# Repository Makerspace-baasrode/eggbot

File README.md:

# eggbot
a drawing machine using eggs as a canvas

This is a project that started in with a build about 10 years ago.
So in this repository you will find a section of old reference files, of which I can not guarantee that they are still functional. But I rather include them to let you wander around to discover what is our there.
I know that a lot of the software will no longere be functional and needs an update, but I'd liked to keep them here as a reference to what was used 10+ years ago

The new build we are attempting in 2025 will be in the top level. 
It will be structured in the several technices we are going to use, CAD-model, 3D-print, laser cutting, PCB design, PCB assembling, ...

If there is any suggestion to organize it differently please let me know

## original project

this project is a make over of the [Eval Mad Scientists](https://shop.evilmadscientist.com/productsmenu/766) eggbot project. All credits go to them as the originators of the ideas. (https://hackaday.com/2019/04/17/what-can-you-learn-from-an-eggbot/)

## refenced links
### The original
- [The Original Egg-Bot Kit](https://wiki.evilmadscientist.com/The_Original_Egg-Bot_Kit)

### 3D prints
- [Enhanced penholder for SphereBot](https://www.thingiverse.com/thing:13407)
- [Laser Cut Sphere-o-bot](https://www.thingiverse.com/thing:368403#files)
- [Laser Cut Sphere-o-bot Instructables](https://www.instructables.com/Laser-Cut-Sphere-O-Bot/)
- [Fischer Technik Eggbot](https://www.thingiverse.com/thing:8109)
- [Eggcup holders for SphereBot / Completely Printable Eggbot](https://www.thingiverse.com/thing:13960)
- [Completely printable Egg-drawer](https://www.thingiverse.com/thing:7988)
- [Finucane Derivative Eggbot](https://www.thingiverse.com/thing:65753)

### Drawing
- [StippleGen](https://wiki.evilmadscientist.com/StippleGen)
- [StippleGen: Weighted Voronoi](https://www.evilmadscientist.com/2012/stipplegen-weighted-voronoi-stippling-and-tsp-paths-in-processing/)
- [code and designs](https://github.com/davidbliss/eggbot)

### Software
- [SphereBotSenderProcessing](https://github.com/zaggo/SphereBotSenderProcessing)
- [Eggduino](https://github.com/cocktailyogi/EggDuino/)
- [Eggbotsimulator](https://github.com/gabber1/EggbotSimulator)
- [EBB Commands](https://www.schmalzhaus.com/EBB/EBBCommands.html)

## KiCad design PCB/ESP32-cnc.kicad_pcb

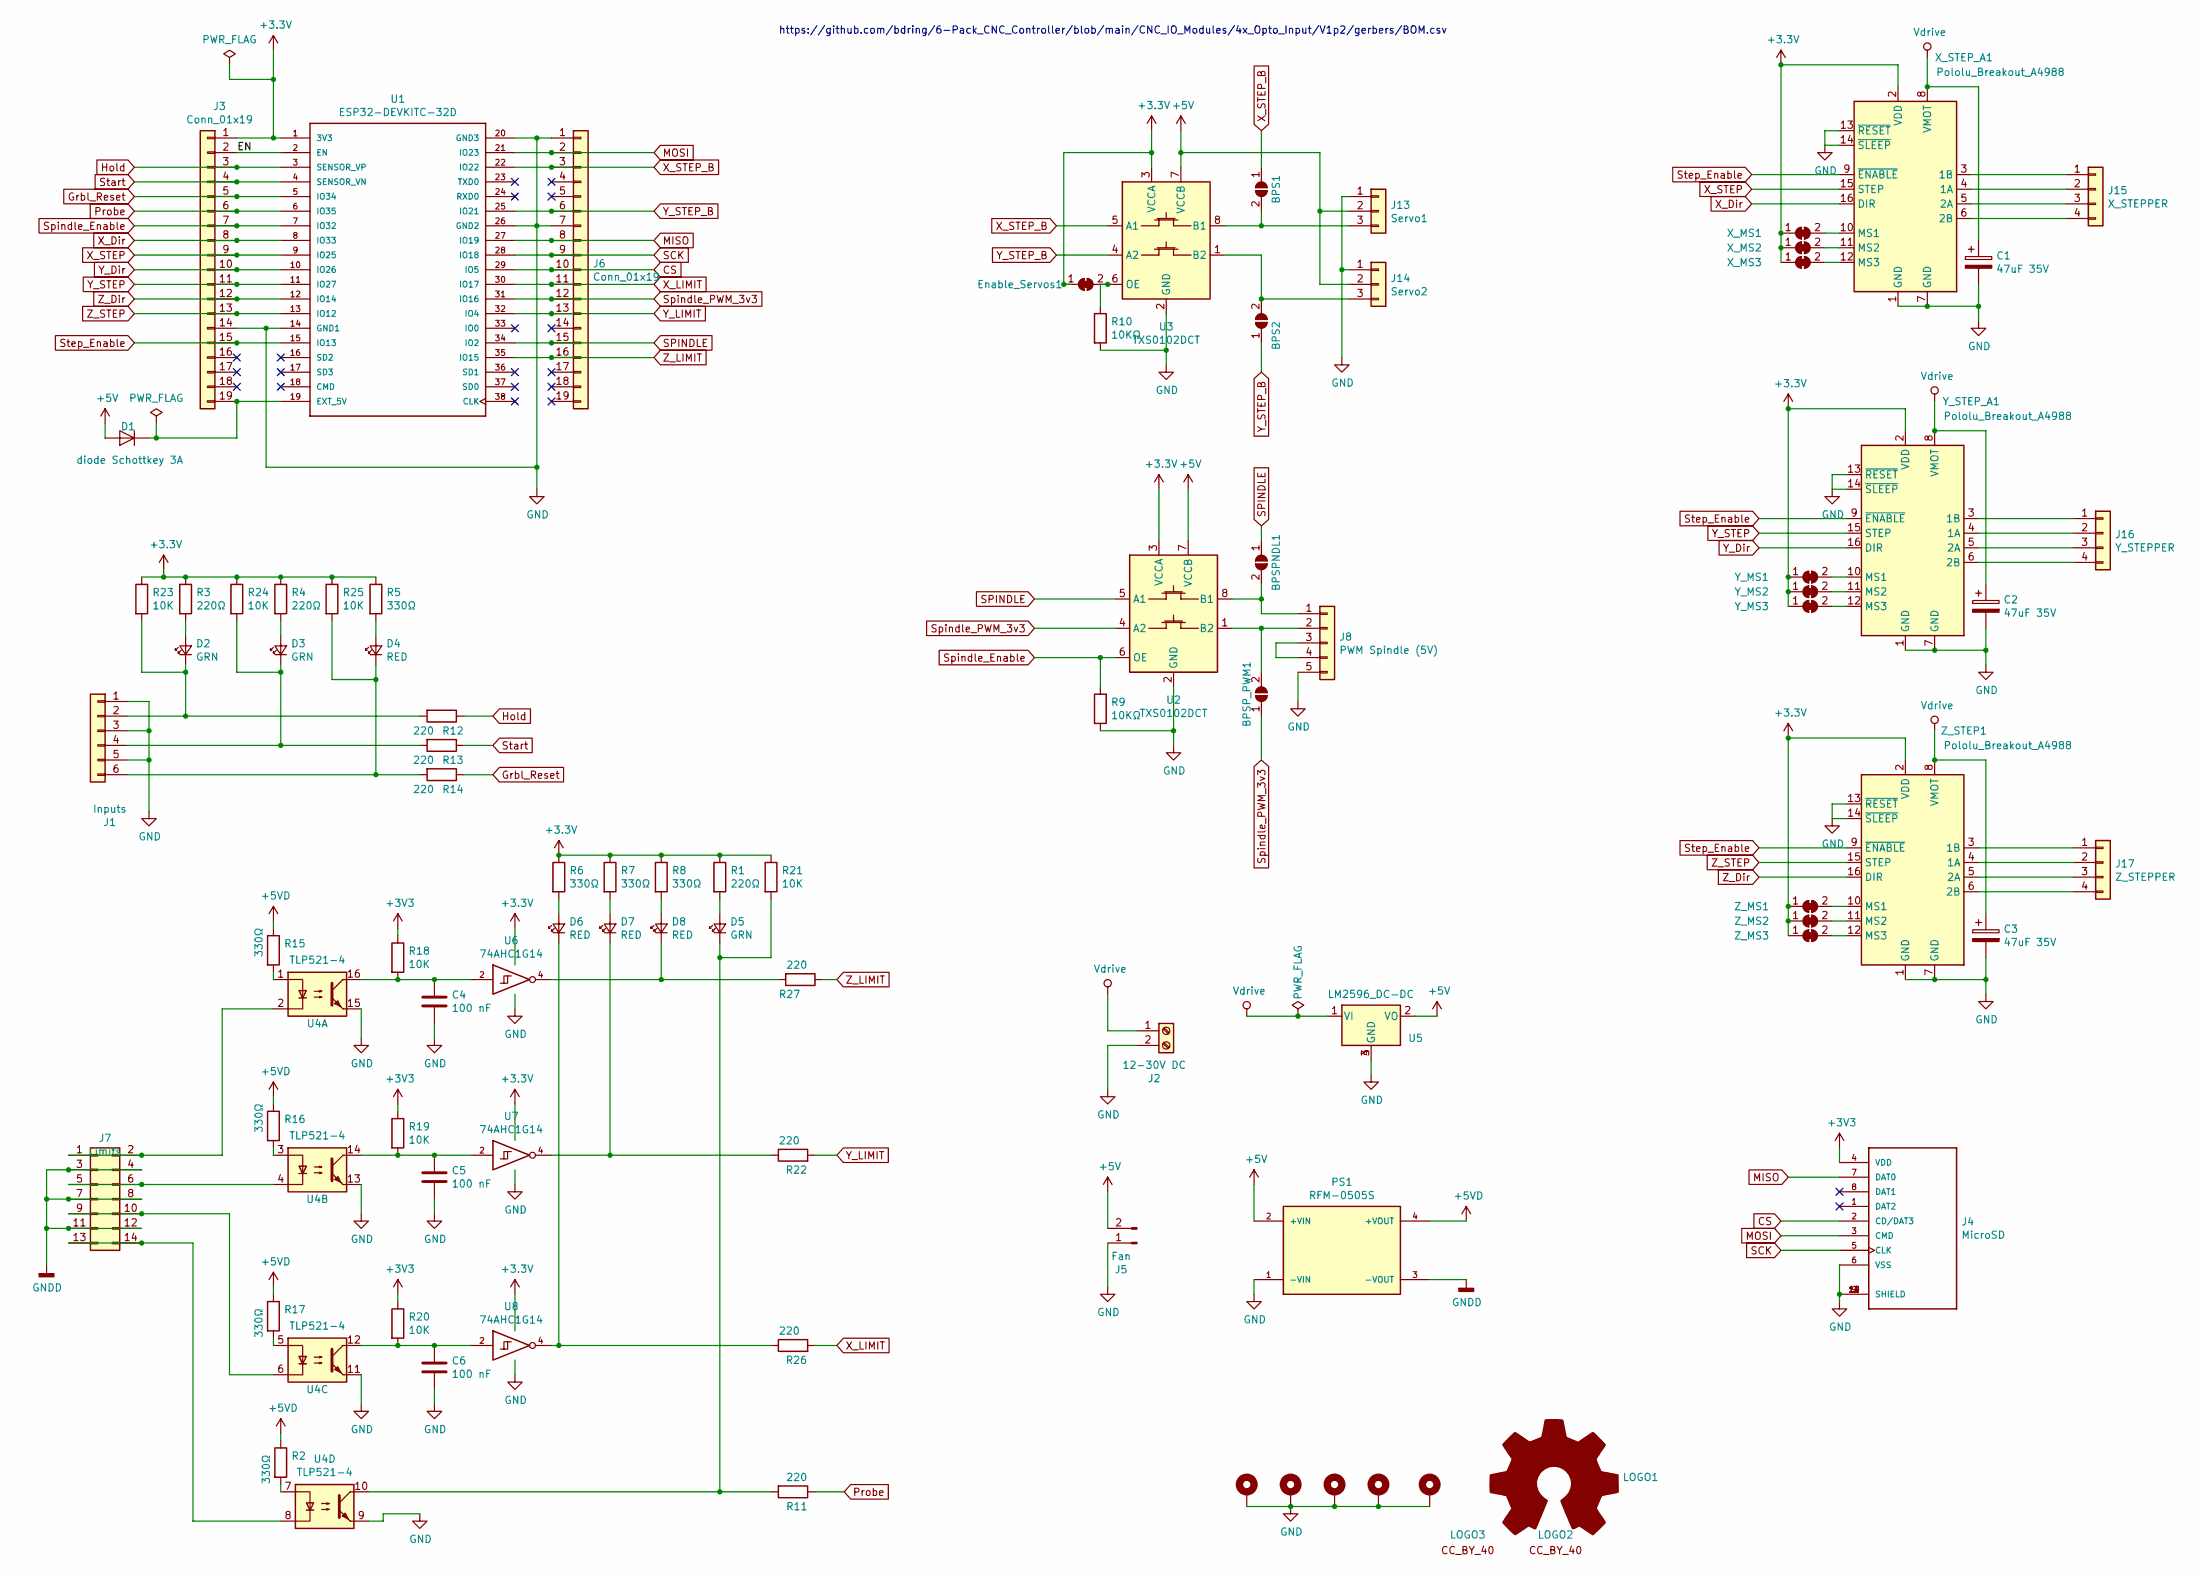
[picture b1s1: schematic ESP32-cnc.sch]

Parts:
BPS1: SERVO1; SolderJumper-2_P1.3mm_Open_TrianglePad1.0x1.5mm
BPS2: SERVO2; SolderJumper-2_P1.3mm_Open_TrianglePad1.0x1.5mm
BPSPNDL1: SPNDL_ON; SolderJumper-2_P1.3mm_Open_TrianglePad1.0x1.5mm
BPSP_PWM1: SPNDL_PWM; SolderJumper-2_P1.3mm_Open_TrianglePad1.0x1.5mm
C1, C2, C3: 47uF 35V; CP_Radial_D10.0mm_P5.00mm; LCSC C134832
C4, C5, C6: 100 nF; C_0805_2012Metric_Pad1.15x1.40mm_HandSolder
D1: diode Schottkey 3A; D_SMA; LCSC C64982
D2, D3, D5: GRN; LED_1206_HandSoldering
D4, D6, D7, D8: RED; LED_1206_HandSoldering
Enable_Servos1: Enable_Servos; SolderJumper-2_P1.3mm_Bridged_RoundedPad1.0x1.5mm
H1, H2, H3, H4, H5: MountingHole_Pad; MountingHole_8.4mm_M8_Pad_Via
J1: Inputs; PinHeader_1x06_P2.54mm_Vertical
J2: 12-30V DC; TerminalBlock_Altech_AK300-2_P5.00mm
J3, J6: Conn_01x19; PinHeader_1x19_P2.54mm_Vertical
J4: MicroSD; GCT_MEM2067-02-180-00-A_REVB; LCSC C91145
J5: Fan; PinHeader_1x02_P2.54mm_Vertical
J7: Limits; PinHeader_2x07_P2.54mm_Vertical
J8: PWM Spindle (5V); PinHeader_1x05_P2.54mm_Vertical
J13: Servo1; PinHeader_1x03_P2.54mm_Vertical
J14: Servo2; PinHeader_1x03_P2.54mm_Vertical
J15: X_STEPPER; PinHeader_1x04_P2.54mm_Vertical
J16: Y_STEPPER; PinHeader_1x04_P2.54mm_Vertical
J17: Z_STEPPER; PinHeader_1x04_P2.54mm_Vertical
LOGO1: Logo_Open_Hardware_Large; OSHW-Symbol_22.3x20mm_SilkScreen
LOGO2: SYM_CC_BY; Symbol_CreativeCommonsPublicDomain_SilkScreenTop_Small
LOGO3: SYM_CC_BY; Symbol_CC-Attribution_CopperTop_Small
PS1: RFM-0505S; CONV_RFM-0505S; PARTREV 0
R1, R3, R4: 220Ω; R_0805_2012Metric_Pad1.15x1.40mm_HandSolder
R2, R5, R6, R7, R8, R15, R16, R17: 330Ω; R_0805_2012Metric_Pad1.15x1.40mm_HandSolder
R9, R10: 10KΩ; R_0805_2012Metric_Pad1.15x1.40mm_HandSolder; LCSC C140868
R11, R12, R13, R14, R22, R26, R27: 220; R_0805_2012Metric_Pad1.15x1.40mm_HandSolder
R18, R19, R20, R21, R23, R24, R25: 10K; R_0805_2012Metric_Pad1.15x1.40mm_HandSolder
U1: ESP32-DEVKITC-32D; MODULE_ESP32-DEVKITC-32D
U2, U3: TXS0102DCT; SOP65P400X130-8N; LCSC C324082
U4: TLP521-4; DIP-16_W7.62mm_LongPads; lcsc C191333
U5: LM2596_DC-DC; LM2596_DC_DC_Step_Down_Module
U6, U7, U8: 74AHC1G14; SOT-23-5
X_MS1: X_MS1; SolderJumper-2_P1.3mm_Bridged_RoundedPad1.0x1.5mm
X_MS2: X_MS2; SolderJumper-2_P1.3mm_Bridged_RoundedPad1.0x1.5mm
X_MS3: X_MS3; SolderJumper-2_P1.3mm_Bridged_RoundedPad1.0x1.5mm
X_STEP_A1: Pololu_Breakout_A4988; MODULE_A4988_STEPPER_MOTOR_DRIVER_CARRIER
Y_MS1: Y_MS1; SolderJumper-2_P1.3mm_Bridged_RoundedPad1.0x1.5mm
Y_MS2: Y_MS2; SolderJumper-2_P1.3mm_Bridged_RoundedPad1.0x1.5mm
Y_MS3: Y_MS3; SolderJumper-2_P1.3mm_Bridged_RoundedPad1.0x1.5mm
Y_STEP_A1: Pololu_Breakout_A4988; MODULE_A4988_STEPPER_MOTOR_DRIVER_CARRIER
Z_MS1: Z_MS1; SolderJumper-2_P1.3mm_Bridged_RoundedPad1.0x1.5mm
Z_MS2: Z_MS2; SolderJumper-2_P1.3mm_Bridged_RoundedPad1.0x1.5mm
Z_MS3: Z_MS3; SolderJumper-2_P1.3mm_Bridged_RoundedPad1.0x1.5mm
Z_STEP1: Pololu_Breakout_A4988; MODULE_A4988_STEPPER_MOTOR_DRIVER_CARRIER

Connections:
+5V: D1.2 (A), J5.2, J13.2, J14.2, PS1.2 (+VIN), U2.7 (VCCB), U3.7 (VCCB), U5.2 (VO)
+5VD: PS1.4 (+VOUT), R2.1, R15.1, R16.1, R17.1
/EN: J3.2, U1.2 (EN)
CS: J4.2 (CD/DAT3), J6.10, U1.29 (IO5)
GND: C1.2, C2.2, C3.2, C4.2, C5.2, C6.2, H1.1, H2.1, H3.1, H4.1, H5.1, J1.1, J1.3, J1.5, J2.2, J3.14, J4.6 (VSS), J4.9 (SHIELD), J4.10 (SHIELD), J4.11 (SHIELD), J4.12 (SHIELD), J5.1, J6.1, J6.7, J8.5, J13.1, J14.1, PS1.1 (-VIN), R9.2, R10.2, U1.14 (GND1), U1.20 (GND3), U1.26 (GND2), U2.2 (GND), U3.2 (GND), U4.9, U4.11, U4.13, U4.15, U5.3 (GND), U5.4 (GND), U6.3 (GND), U7.3 (GND), U8.3 (GND), X_STEP_A1.1 (GND), X_STEP_A1.7 (GND), X_STEP_A1.13 (~RESET), X_STEP_A1.14 (~SLEEP), Y_STEP_A1.1 (GND), Y_STEP_A1.7 (GND), Y_STEP_A1.13 (~RESET), Y_STEP_A1.14 (~SLEEP), Z_STEP1.1 (GND), Z_STEP1.7 (GND), Z_STEP1.13 (~RESET), Z_STEP1.14 (~SLEEP)
GNDD: J7.3, J7.4, J7.7, J7.8, J7.11, J7.12, PS1.3 (-VOUT)
Grbl_Reset: J3.5, R14.1, U1.5 (IO34)
Hold: J3.3, R12.1, U1.3 (SENSOR_VP)
MISO: J4.7 (DAT0), J6.8, U1.27 (IO19)
MOSI: J4.3 (CMD), J6.2, U1.21 (IO23)
unnamed: BPS1.2 (B), J13.3, U3.8 (B1)
unnamed: BPS2.2 (B), J14.3, U3.1 (B2)
unnamed: BPSPNDL1.2 (B), J8.1, U2.8 (B1)
unnamed: BPSP_PWM1.2 (B), J8.2, U2.1 (B2)
unnamed: C4.1, R18.2, U4.16, U6.2
unnamed: C5.1, R19.2, U4.14, U7.2
unnamed: C6.1, R20.2, U4.12, U8.2
unnamed: D1.1 (K), J3.19, U1.19 (EXT_5V)
unnamed: D2.1 (K), J1.2, R12.2, R23.2
unnamed: D2.2 (A), R3.2
unnamed: D3.1 (K), J1.4, R13.2, R24.2
unnamed: D3.2 (A), R4.2
unnamed: D4.1 (K), J1.6, R14.2, R25.2
unnamed: D4.2 (A), R5.2
unnamed: D5.1 (K), R11.2, R21.2, U4.10
unnamed: D5.2 (A), R1.2
unnamed: D6.1 (K), R26.1, U8.4
unnamed: D6.2 (A), R6.2
unnamed: D7.1 (K), R22.1, U7.4
unnamed: D7.2 (A), R7.2
unnamed: D8.1 (K), R27.2, U6.4
unnamed: D8.2 (A), R8.2
unnamed: Enable_Servos1.2 (B), R10.1, U3.6 (OE)
unnamed: J7.1, J7.2, U4.2
unnamed: J7.5, J7.6, U4.4
unnamed: J7.9, J7.10, U4.6
unnamed: J7.13, J7.14, U4.8
unnamed: J8.3, J8.4
unnamed: J15.1, X_STEP_A1.3 (1B)
unnamed: J15.2, X_STEP_A1.4 (1A)
unnamed: J15.3, X_STEP_A1.5 (2A)
unnamed: J15.4, X_STEP_A1.6 (2B)
unnamed: J16.1, Y_STEP_A1.3 (1B)
unnamed: J16.2, Y_STEP_A1.4 (1A)
unnamed: J16.3, Y_STEP_A1.5 (2A)
unnamed: J16.4, Y_STEP_A1.6 (2B)
unnamed: J17.1, Z_STEP1.3 (1B)
unnamed: J17.2, Z_STEP1.4 (1A)
unnamed: J17.3, Z_STEP1.5 (2A)
unnamed: J17.4, Z_STEP1.6 (2B)
unnamed: R2.2, U4.7
unnamed: R15.2, U4.1
unnamed: R16.2, U4.3
unnamed: R17.2, U4.5
unnamed: X_MS1.2 (B), X_STEP_A1.10 (MS1)
unnamed: X_MS2.2 (B), X_STEP_A1.11 (MS2)
unnamed: X_MS3.2 (B), X_STEP_A1.12 (MS3)
unnamed: Y_MS1.2 (B), Y_STEP_A1.10 (MS1)
unnamed: Y_MS2.2 (B), Y_STEP_A1.11 (MS2)
unnamed: Y_MS3.2 (B), Y_STEP_A1.12 (MS3)
unnamed: Z_MS1.2 (B), Z_STEP1.10 (MS1)
unnamed: Z_MS2.2 (B), Z_STEP1.11 (MS2)
unnamed: Z_MS3.2 (B), Z_STEP1.12 (MS3)
Probe: J3.6, R11.1, U1.6 (IO35)
SCK: J4.5 (CLK), J6.9, U1.28 (IO18)
SPINDLE: BPSPNDL1.1 (A), J6.15, U1.34 (IO2), U2.5 (A1)
Spindle_Enable: J3.7, R9.1, U1.7 (IO32), U2.6 (OE)
Spindle_PWM_3v3: BPSP_PWM1.1 (A), J6.12, U1.31 (IO16), U2.4 (A2)
Start: J3.4, R13.1, U1.4 (SENSOR_VN)
Step_Enable: J3.15, U1.15 (IO13), X_STEP_A1.9 (~ENABLE), Y_STEP_A1.9 (~ENABLE), Z_STEP1.9 (~ENABLE)
Vdrive: C1.1, C2.1, C3.1, J2.1, U5.1 (VI), X_STEP_A1.8 (VMOT), Y_STEP_A1.8 (VMOT), Z_STEP1.8 (VMOT)
X_Dir: J3.8, U1.8 (IO33), X_STEP_A1.16 (DIR)
X_LIMIT: J6.11, R26.2, U1.30 (IO17)
X_STEP: J3.9, U1.9 (IO25), X_STEP_A1.15 (STEP)
X_STEP_B: BPS1.1 (A), J6.3, U1.22 (IO22), U3.5 (A1)
Y_Dir: J3.10, U1.10 (IO26), Y_STEP_A1.16 (DIR)
Y_LIMIT: J6.13, R22.2, U1.32 (IO4)
Y_STEP: J3.11, U1.11 (IO27), Y_STEP_A1.15 (STEP)
Y_STEP_B: BPS2.1 (A), J6.6, U1.25 (IO21), U3.4 (A2)
Z_Dir: J3.12, U1.12 (IO14), Z_STEP1.16 (DIR)
Z_LIMIT: J6.16, R27.1, U1.35 (IO15)
Z_STEP: J3.13, U1.13 (IO12), Z_STEP1.15 (STEP)

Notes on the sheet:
https://github.com/bdring/6-Pack_CNC_Controller/blob/main/CNC_IO_Modules/4x_Opto_Input/V1p2/gerbers/BOM.csv

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
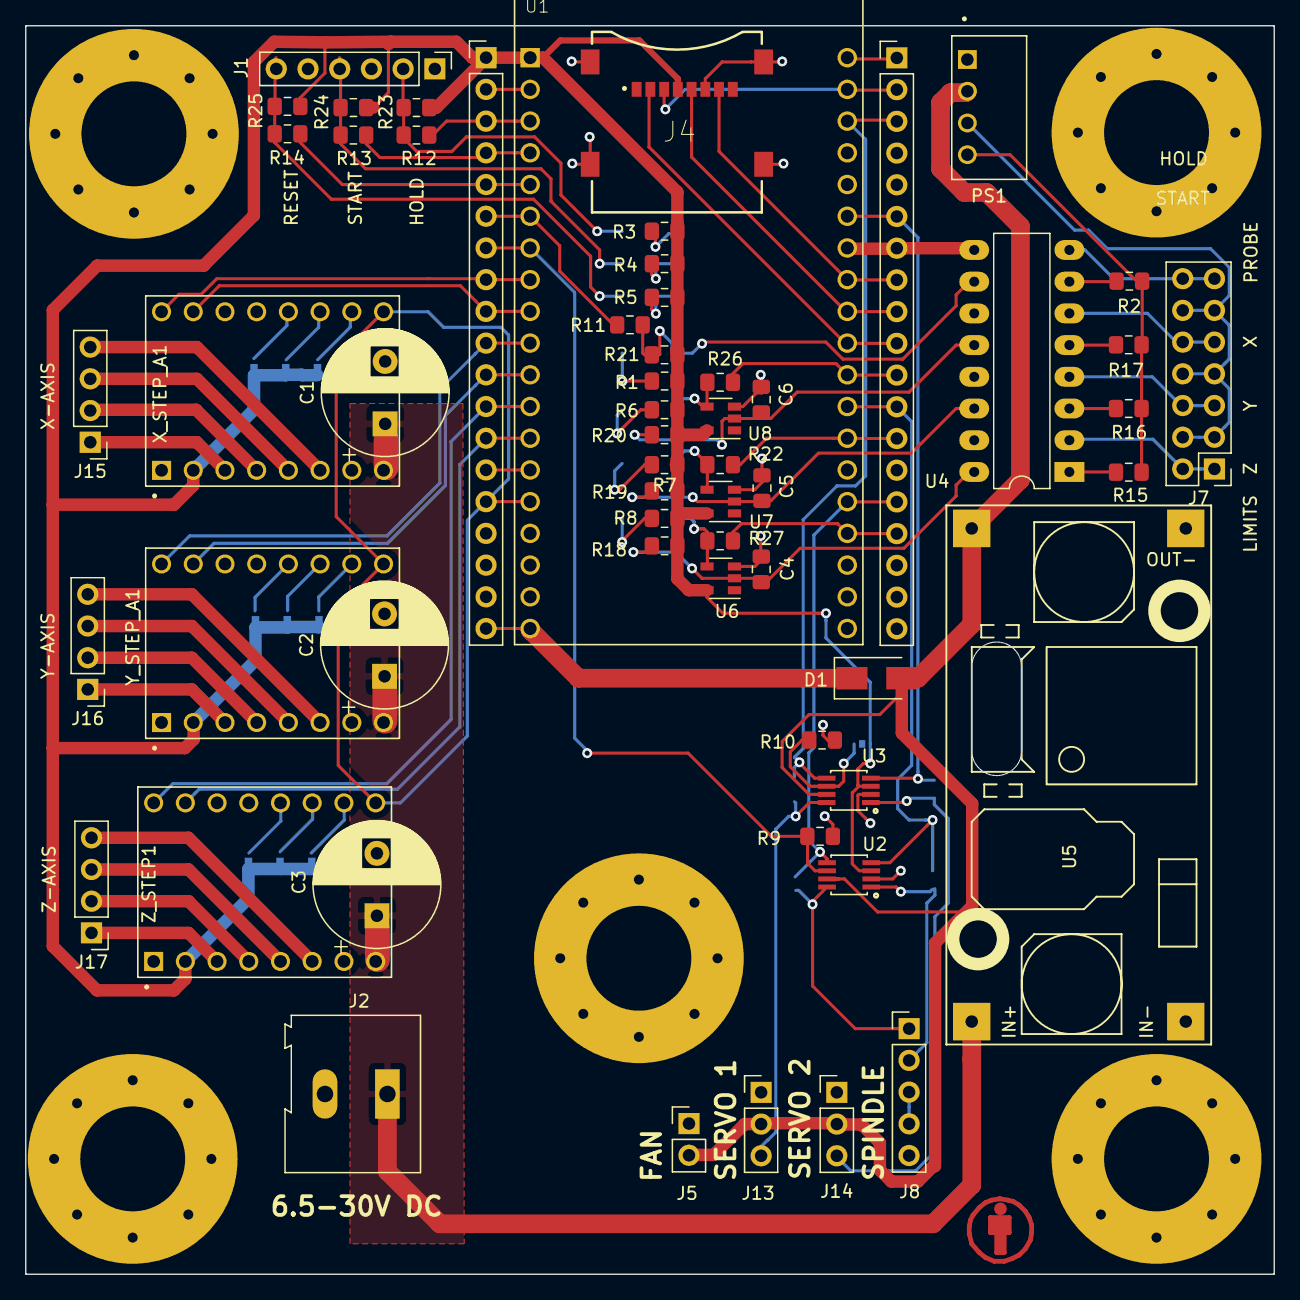
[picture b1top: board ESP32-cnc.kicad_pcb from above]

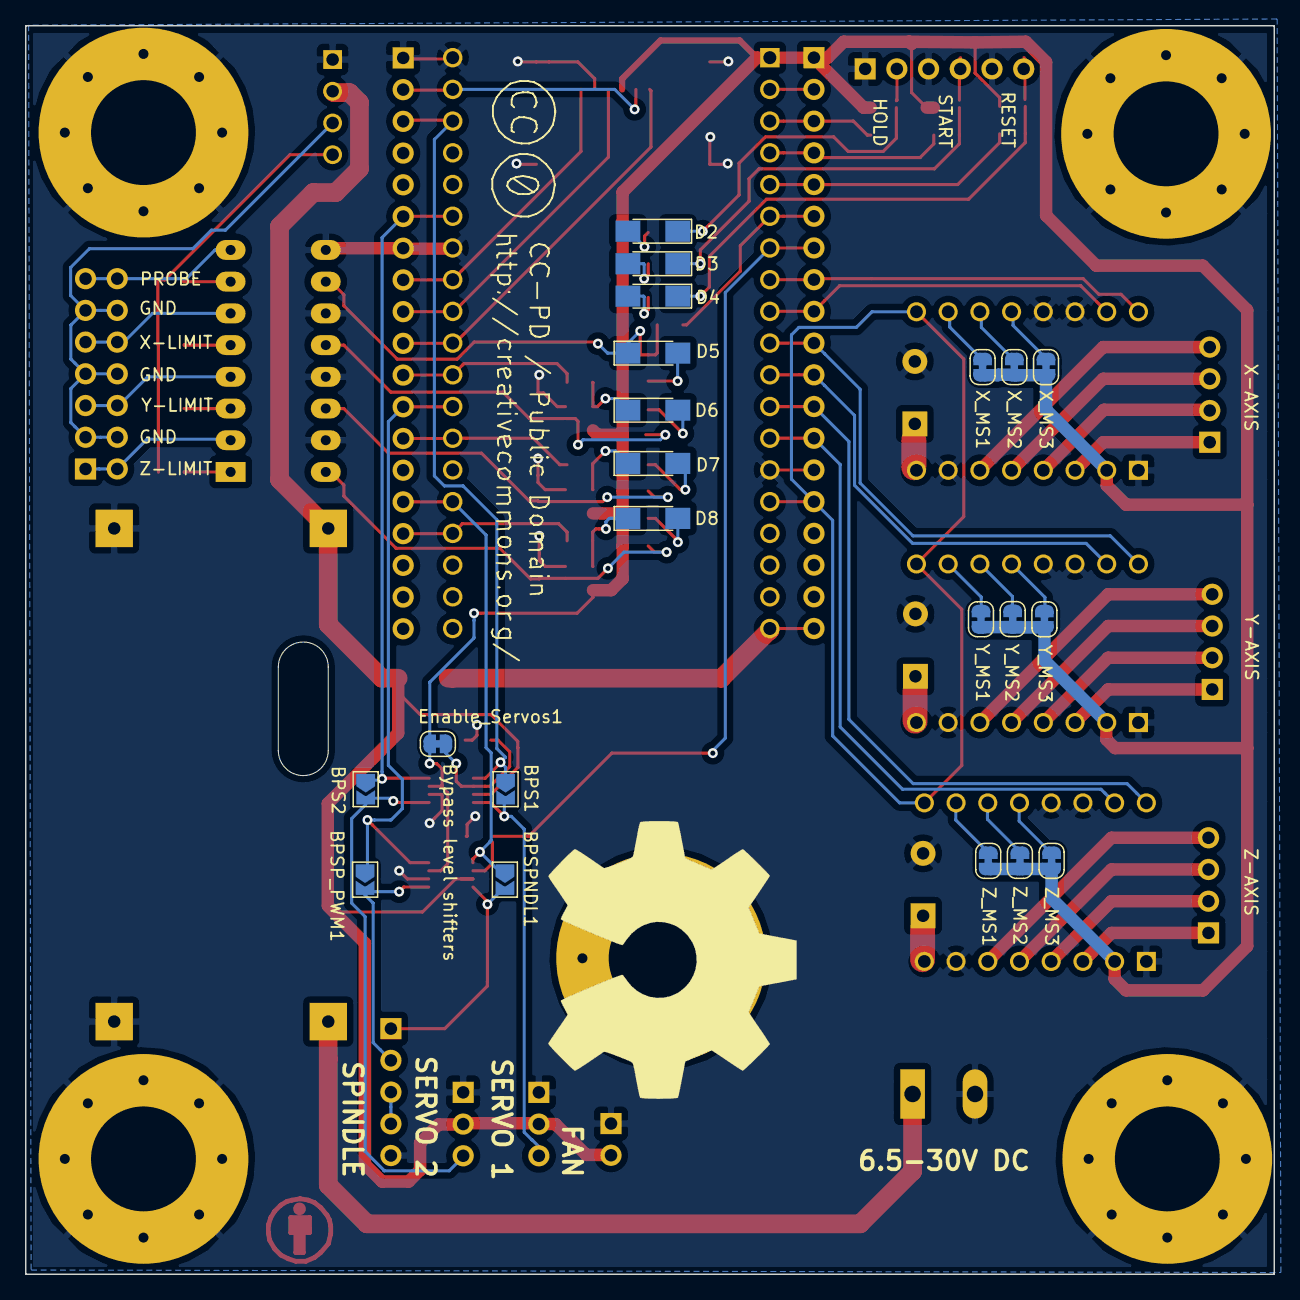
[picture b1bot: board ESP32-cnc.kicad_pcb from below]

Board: 2 copper layers, 100.0 x 100.0 mm, 88 parts (23 on the bottom side), 83 nets.

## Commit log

2025-02-01 reference projects
    added old reference projects
2025-02-01 3D parts
    3D printable and CAD model
2025-02-01 renamed CAD directory
    renamed CAD directury
    to reflect the CAD software used
2025-02-01 added link
2025-02-01 corrected link
2025-02-01 updated links
2025-02-01 closing bracket
2025-02-01 headings
2025-02-01 lines
2025-02-01 links
2025-02-01 use of inserts
2025-02-01 added instructables
2025-02-02 PCB adjustment
    needed 18mm for mounting holes M8
2025-02-09 PCB design
    updated 3D design to purchased parts
    use M4 inserts instead of M4 nuts
    Kicad V5. design of PCB
2025-02-17 speling aangepast
    speling voor motor as aangepast en fout in fusion opgelost
2025-02-20 adjustments
    adjustments
2025-02-21 production files
2025-02-21 upate naar echte componenten
2025-02-23 update 3D print STL files
2025-02-23 table update
2025-02-23 corrected mark down table
2025-02-23 show print info
2025-03-02 exploded view
2025-03-03 pdf version
2025-03-03 exploded views
2025-03-08 exploded view pen houder.
2025-03-23 Create config.yaml
    config file from Geert
2025-03-23 typo
